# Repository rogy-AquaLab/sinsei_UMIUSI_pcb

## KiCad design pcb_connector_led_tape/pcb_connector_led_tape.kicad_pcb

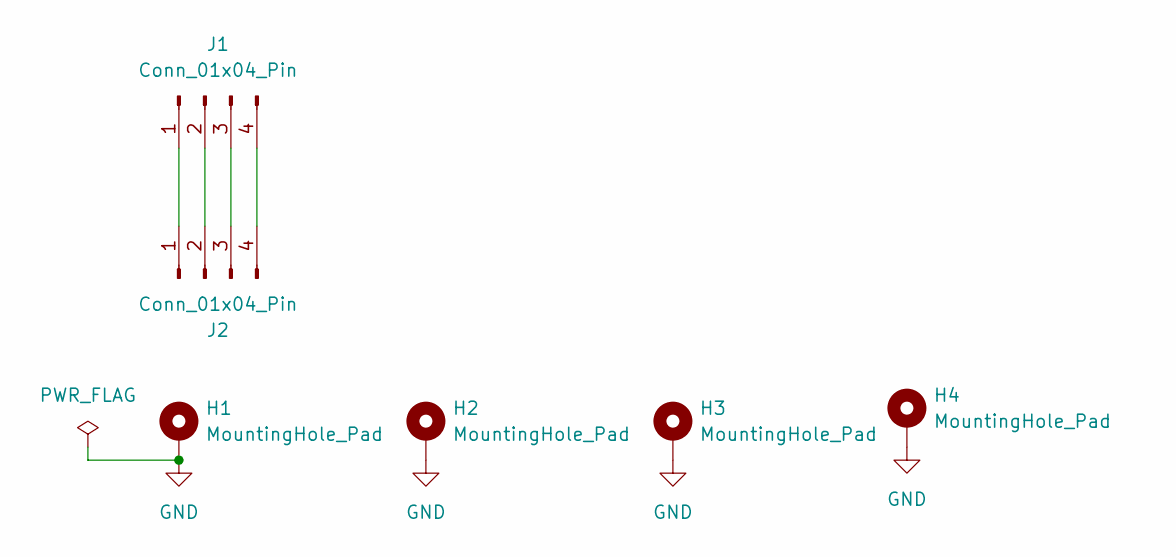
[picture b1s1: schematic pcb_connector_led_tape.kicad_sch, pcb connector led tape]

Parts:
H1, H2, H3, H4: MountingHole_Pad; MountingHole_3.2mm_M3_PAD_for_spacer
J1, J2: Conn_01x04_Pin; PinHeader_1x04_P2.00mm_Vertical

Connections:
GND: H1.1, H2.1, H3.1, H4.1
unnamed: J1.1, J2.1
unnamed: J1.2, J2.2
unnamed: J1.3, J2.3
unnamed: J1.4, J2.4

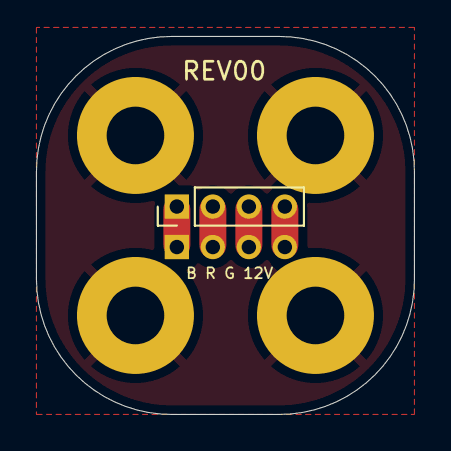
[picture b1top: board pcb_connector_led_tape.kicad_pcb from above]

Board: 2 copper layers, 21.0 x 21.0 mm, 6 parts (1 on the bottom side), 5 nets.

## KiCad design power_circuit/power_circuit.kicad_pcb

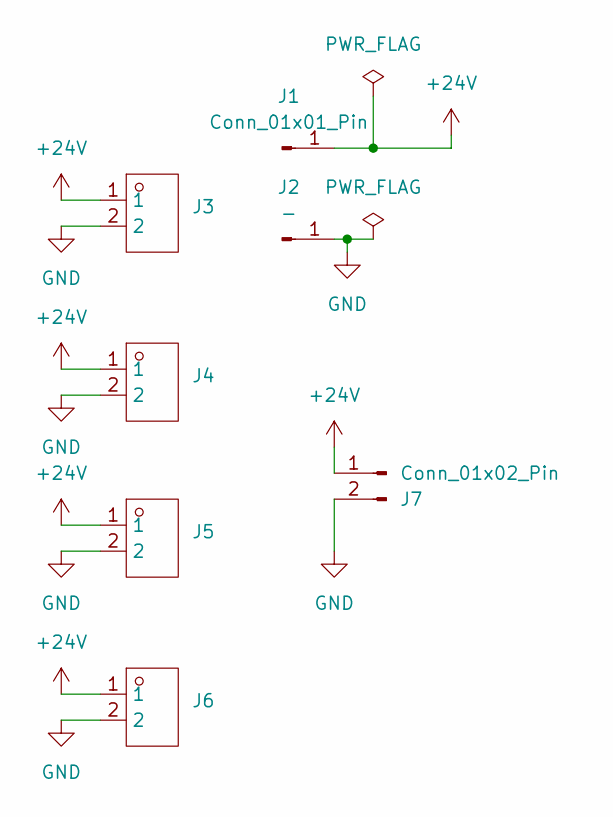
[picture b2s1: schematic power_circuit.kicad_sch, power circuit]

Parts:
J1: Conn_01x01_Pin; MountingHole_4.5mm_Pad_Via
J2: -; MountingHole_4.5mm_Pad_Via
J3, J4, J5, J6: TH_XT90PB-F; Manufacturer Part XT90H-F.G.Y; LCSC Part Name 两件套 AMASS(艾迈斯)焊接注塑型 2PIN 接头XT90H-F.G.Y
J7: Conn_01x02_Pin; JST_VH_B2PS-VH_1x02_P3.96mm_Horizontal

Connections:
+24V: J1.1, J3.1, J4.1, J5.1, J6.1, J7.1
GND: J2.1, J3.2, J4.2, J5.2, J6.2, J7.2

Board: 2 copper layers, 7 parts (0 on the bottom side), 2 nets, no tracks yet.

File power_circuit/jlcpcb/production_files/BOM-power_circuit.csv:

Comment,Designator,Footprint,LCSC,Quantity
Conn_01x02_Pin,J7,JST_VH_B2PS-VH_1x02_P3.96mm_Horizontal,,1
-,J2,MountingHole_4.5mm_Pad_Via,,1
Conn_01x01_Pin,J1,MountingHole_4.5mm_Pad_Via,,1
~,J5,TH_XT90PB-F,,1
~,J3,TH_XT90PB-F,,1
~,J4,TH_XT90PB-F,,1
~,J6,TH_XT90PB-F,,1
